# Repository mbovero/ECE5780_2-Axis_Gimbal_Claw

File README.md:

### Team Members
* Miles Bovero
* Lawrence Ponce
* Brian Stites
* Burke Dambly
  
# 2-Axis Gimbal System using BNO085 and TMC2209

This project implements a 2-axis gimbal system powered by NEMA 17 stepper motors, a custom TMC2209 stepper driver, and the BNO085 IMU, all controlled by an STM32F0 microcontroller. The system supports both **manual joystick control** and **automatic gimbal stabilization** using quaternion feedback from the IMU.

## Features

- **Automatic stabilization** using BNO085 quaternion output (Rotation Vector).
- **Manual override mode** via joystick input.
- **Custom driver logic** for TMC2209 stepper controllers (no libraries).
- **Status indication** using onboard LEDs:
  - 🟢 **Green**: System ready
  - 🟡 **Yellow**: Manual mode
  - 🔴 **Red**: Gimbal stabilization mode

## Hardware

- **Parts List:** https://docs.google.com/spreadsheets/d/1ASUmAiZSFDpc-IezaZOCM-j6GSmX4DIoBAKoNAnrK8I/edit?gid=0#gid=0
- **BOM:** https://docs.google.com/spreadsheets/d/1F1Fa0VNCSiJDzJphaV6HfyEmqR7Gyjhc7J4WnCEqq48/edit?usp=sharing

## Control Logic

- System starts in **gimbal mode**. The initial orientation is stored as the target.
- A joystick button press toggles between **manual** and **gimbal** mode.
- In **manual mode**, the joystick directly sets direction and speed of the motors.
- In **gimbal mode**, real-time quaternion feedback from the IMU drives motors to minimize roll and yaw error.
- The STM32 blue on-board button acts as a **kill switch**, freezing the system until reset.

## Project Structure

- `main.c` – Main call to control function.
- `bno085.c/h` – IMU I2C interface and quaternion parsing logic.
- `motor_control.c/h` – Low-level motor driver setup and PWM control.
- `quaternion.c/h` – Roll and yaw error computation from quaternion deltas.
- `gimbal_controller.c/h` – Core application logic for managing gimbal behavior, mode switching, LED indicators, and overall control flow between manual and automatic stabilization.
- `joystick.c/h` – ADC interface for reading joystick analog input.

## Flow Chart

## Capabilities

- Real-time stabilization on **roll and yaw axes** using quaternion feedback from the BNO085 IMU.
- Responsive **manual control** through a 2-axis joystick.
- Intelligent speed scaling and jitter prevention based on calculated orientation error.
- Mode switching with software debouncing: easily toggle between manual and gimbal modes.
- Visual mode indication via red (manual) and yellow (gimbal) LEDs, and a green LED for system readiness.
- **Kill switch functionality** to safely disable the system at any time.

### Limitations

- The current mechanical setup limits **full-range roll rotation**. Due to the gimbal frame geometry, the roll axis cannot rotate completely while maintatining yaw logic without mechanical interference.
- All quaternion math is handled using **fixed-point arithmetic**, which prioritizes performance on the STM32F0 but limits precision.

## Setup

1. **Wiring:**
   - **Wiring Diagram:** https://drive.google.com/file/d/1Tr6oJw9C9LlnuBq3UyTGPtjXQ-eJ-zLg/view?usp=sharing
   - See Wiring section below for more details

2. **Flashing:**
   - Use Platformio in VS Code to Flash board.
   - Run `platformio run -e gimbal_controller -t upload` in the Platformio terminal.

3. **Start Sequence:**
   - Wait for the **green LED** to turn on (IMU ready).
   - Press joystick button to toggle modes.
   - Use the kill switch (blue STM USER button) to halt the system if needed.

## 🔌 Wiring Connections

### STM32 → IMU Wiring

| STM32 Pin | IMU Pin    |
|-----------|------------|
| 3V        | 3V3        |
| GND       | GND        |
| PB14      | SDA / RX   |
| PB13      | SCL / TX   |

### STM32 → Motor Driver Wiring

#### YAW Motor Driver

| STM32 Pin | Motor Driver Pin |
|-----------|------------------|
| PC6       | STEP             |
| PC7       | DIR              |
| PC8       | MS1              |
| PC9       | MS2              |
| PA8       | ENN              |
| GND       | GND              |

#### ROLL Motor Driver

| STM32 Pin | Motor Driver Pin |
|-----------|------------------|
| PB10      | STEP             |
| PB2       | DIR              |
| PB1       | MS1              |
| PB0       | MS2              |
| PC5       | ENN              |
| GND       | GND              |

### STM32 → Joystick Wiring

| STM32 Pin | Joystick Pin |
|-----------|--------------|
| PC3       | VRY          |
| PA5       | VRX          |
| PA1       | SW           |
| 3V        | 5V           |
| GND       | GND          |

### STM32 → LED Wiring

| STM32 Pin | Function                   |
|-----------|----------------------------|
| PB3       | IMU status LED             |
| PB4       | Manual mode indicator LED  |
| PB5       | Gimbal mode indicator LED  |

## Notes
- Quaternion values are in **Q14 format** and processed using fixed-point arithmetic to avoid floating-point dependency.

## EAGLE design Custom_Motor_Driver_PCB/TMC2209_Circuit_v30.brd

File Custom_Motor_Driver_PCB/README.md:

# PCB Layout Preview

# Circuit Schematic
[Circuit Schematic (PDF)](Media/circuit_schematic.pdf)

# 3D PCB Layout Preview

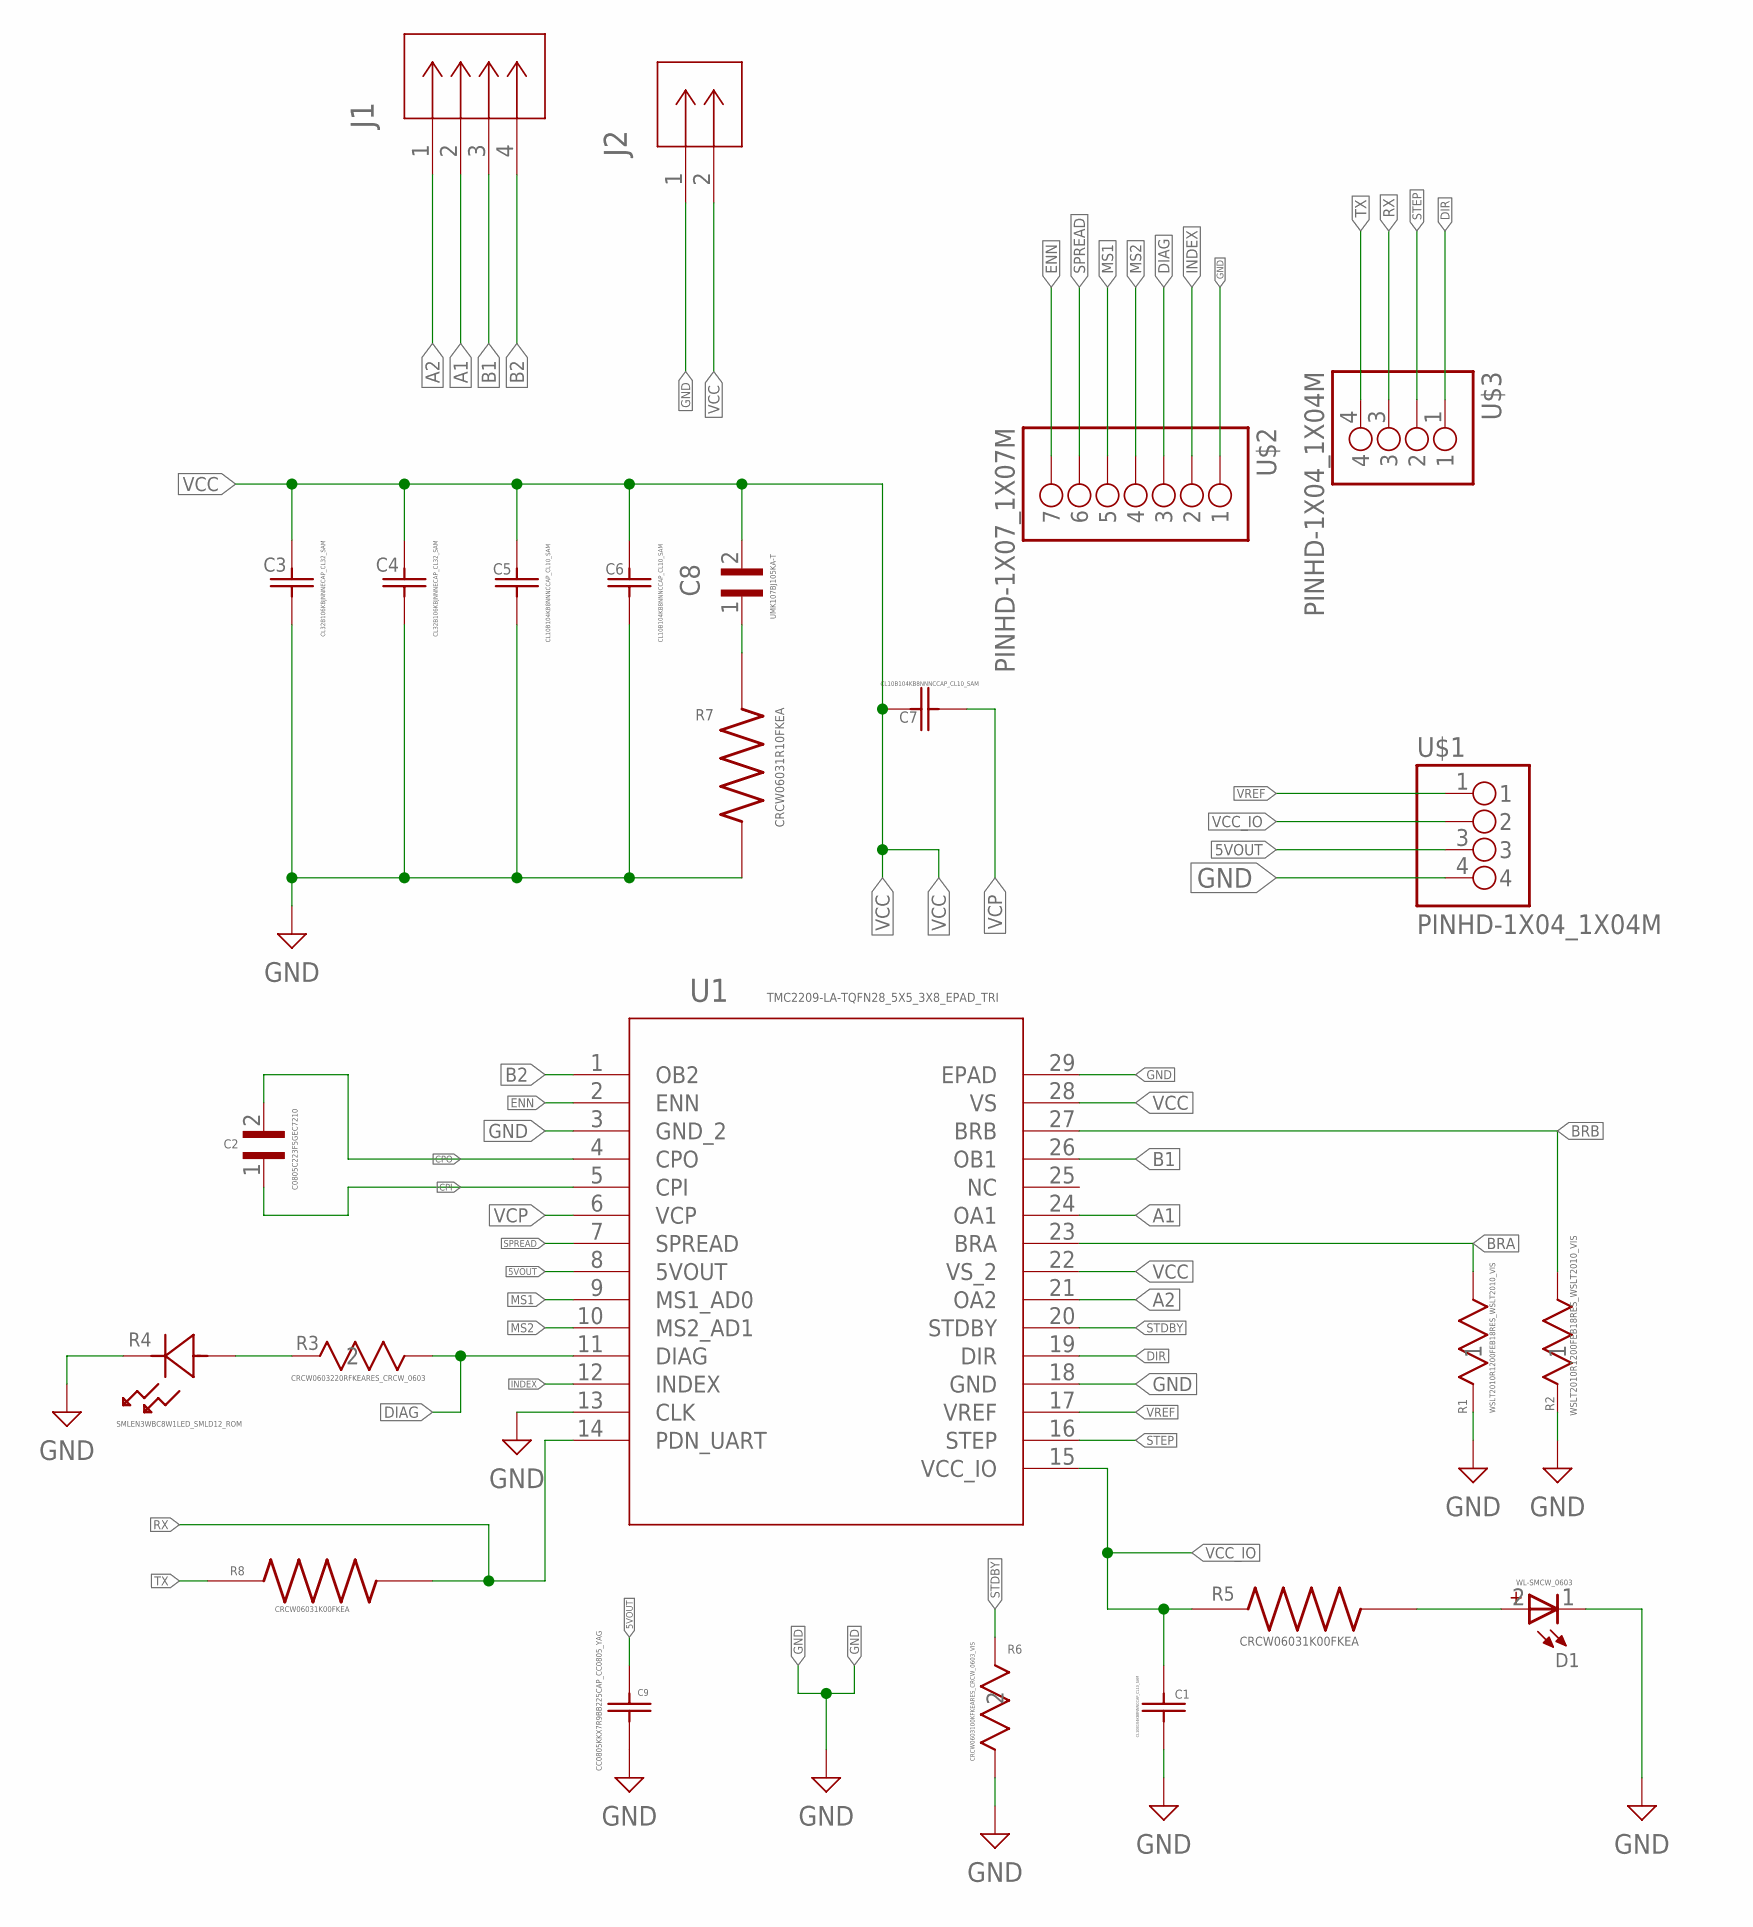
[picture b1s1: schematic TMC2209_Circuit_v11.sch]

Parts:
C1, C5, C6, C7: CL10B104KB8NNNCCAP_CL10_SAM; CAP_CL10_SAM
C2: C0805C223F5GEC7210; CAPC2012X120N
C3, C4: CL32B106KBJNNNECAP_CL32_SAM; CAP_CL32_SAM
C8: UMK107BJ105KA-T; CAPC1608X90N
C9: CC0805KKX7R9BB225CAP_CC0805_YAG; CAP_CC0805_YAG
D1: WL-SMCW_0603
J1: S4B-XH-A(LF)(SN)CONN_S4B-XH-A(LF)(SN)_JST; CONN_S4B-XH-A(LF)(SN)_JST
J2: S2B-PH-K-S(LF)(SN)CONN_S2B-PH-K-S_JST; CONN_S2B-PH-K-S_JST
R1, R2: WSLT2010R1200FEB18RES_WSLT2010_VIS; RES_WSLT2010_VIS
R3: CRCW0603220RFKEARES_CRCW_0603; RES_CRCW_0603
R4: SMLEN3WBC8W1LED_SMLD12_ROM; LED_SMLD12_ROM
R5, R8: CRCW06031K00FKEA; RESC1508X50N
R6: CRCW0603100KFKEARES_CRCW_0603_VIS; RES_CRCW_0603_VIS
R7: CRCW06031R10FKEA; RESC1508X50N
U1: TMC2209-LA-TQFN28_5X5_3X8_EPAD_TRI; QFN28_5X5_3X8_EPAD_TRI
U$1, U$3: PINHD-1X04_1X04M; 1X04
U$2: PINHD-1X07_1X07M; 1X07

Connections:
5VOUT: C9.1, U1.8 (5VOUT), U$1.3
A1: J1.2, U1.24 (OA1)
A2: J1.1, U1.21 (OA2)
B1: J1.3, U1.26 (OB1)
B2: J1.4, U1.1 (OB2)
BRA: R1.2, U1.23 (BRA)
BRB: R2.2, U1.27 (BRB)
CPI: C2.1, U1.5 (CPI)
CPO: C2.2, U1.4 (CPO)
DIAG: R3.1, U1.11 (DIAG), U$2.3
DIR: U1.19 (DIR), U$3.1
ENN: U1.2 (ENN), U$2.7
GND: C1.2, C3.1, C4.1, C5.1, C6.1, C9.2, D1.1 (-), J2.1, R1.1, R2.1, R4.1, R6.1, R7.1, U1.3 (GND_2), U1.13 (CLK), U1.18 (GND), U1.29 (EPAD), U$1.4, U$2.1
INDEX: U1.12 (INDEX), U$2.2
MS1: U1.9 (MS1_AD0), U$2.5
MS2: U1.10 (MS2_AD1), U$2.4
unnamed: R3.2, R4.2
unnamed: D1.2 (+), R5.2
unnamed: C8.1, R7.2
RX: R8.2, U1.14 (PDN_UART), U$3.3
SPREAD: U1.7 (SPREAD), U$2.6
STDBY: R6.2, U1.20 (STDBY)
STEP: U1.16 (STEP), U$3.2
TX: R8.1, U$3.4
VCC: C3.2, C4.2, C5.2, C6.2, C7.2, C8.2, J2.2, U1.22 (VS_2), U1.28 (VS)
VCC_IO: C1.1, R5.1, U1.15 (VCC_IO), U$1.2
VCP: C7.1, U1.6 (VCP)
VREF: U1.17 (VREF), U$1.1

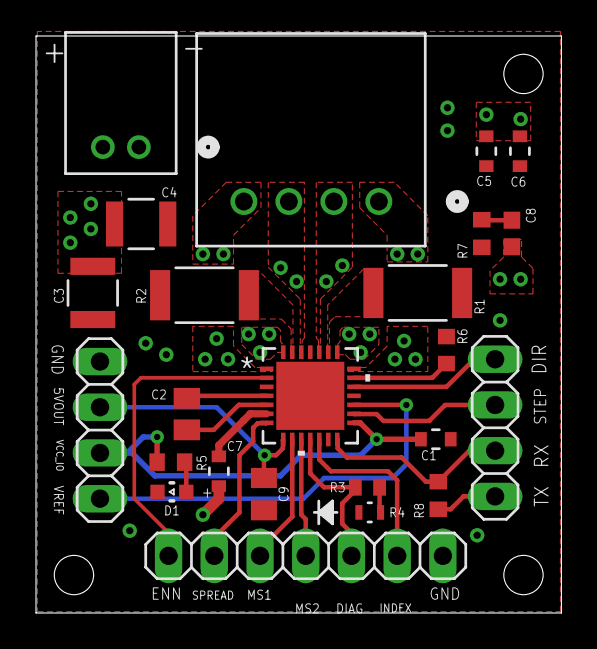
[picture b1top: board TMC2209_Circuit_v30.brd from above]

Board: 4 copper layers, 29.2 x 32.1 mm, 24 parts (0 on the bottom side), 28 nets.

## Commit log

2025-03-22 Added STM32 Infrastructure
2025-03-22 modified the ini file and main to allow for custom file usage. Tested a basic blink functionality to ensure working order
2025-03-23 red led on PWM with flux duty cycle
2025-03-23 Wrote GPIO and register initialization code for I2C communication
2025-03-23 Added stm_imu_i2c
2025-03-24 Configured timer channel 1 on tim3, tim16, and tim17 to output a pwm signal, experimentation is needed on variable speeds/switching directions while fully enabled
2025-03-24 Successfully receiving rotation vector data over I2C
2025-03-27 working joystick
2025-04-05 Added My_HAL_GPIO functions developed during lab.
2025-04-05 Added GPIO RCC clock startup functions
2025-04-05 Implemented I2C/SHTP read and write functions for IMU communication
2025-04-06 Established connection with IMU using custom functions
2025-04-06 Generated LED ouputs based on IMU rotation
2025-04-06 Ignore .vscode folder
2025-04-06 Completed first gimbal system proof-of-concept using LEDs
2025-04-17 Troubleshooting motor driver
2025-04-18 test code for stepper driver in imu_i2c test file
2025-04-19 Deleted unused files
2025-04-19 Created file for testing
2025-04-19 Experimented with dynamic motor control via IMU
2025-04-19 Changed signals for motor testing
2025-04-22 Working gimbal code with reset interrupt
2025-04-22 joystick motor control working
2025-04-23 Created Debug folder to hold debugging code
2025-04-23 Created header file for joystick controls
2025-04-23 Removed unused code files and moved debugging code to Debug folder
2025-04-23 Changed bno085_read_rotation_vector method to handle volatile uints
2025-04-23 Removed redundant and dead code; improved comments
2025-04-23 Refactored joystick code into dedicated file and functions
2025-04-23 Removed unused functions and added new functions for manual (joystick) motor control
2025-04-23 Removed unused constants
2025-04-23 Performed final code cleanup: fixed/improved commenting, added function headers, removed unnecessary or dead code
2025-04-23 Modified header file comments for proper function header previews
2025-04-23 Fixed GPIO pin comments regarding ADC inputs
2025-04-23 better variable speeds
2025-04-23 Fully commented quaternion functions and added a file header...
2025-04-23 Changed GPIO initialization to have consistent formatting
2025-04-23 Fixed spelling errors in comments
2025-04-24 Uploaded custom stepper motor driver files
2025-04-24 Uploaded gimbal 3D model files
2025-04-24 Moved images to new Media folder
2025-04-24 Reorganized media
2025-04-24 Rename Wiring Diagram.jpg to WiringDiagram.jpg
2025-04-24 Rename PreDemoDay_Demonstration (1).gif to PreDemoDay_Demonstration.gif

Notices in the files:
parts and their libraries:
TMC2209_NewFootprint: COPYRIGHT: Copyright (C) 2025 Ultra Librarian. All rights reserved.
